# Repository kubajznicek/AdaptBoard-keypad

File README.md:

# AdaptBoard keypad

Custom macropad with swappable modules, based on Key Boar 2040.

## Features

- swappable modules
- 4x5 customizable grid
- serial communication

#### Different modules
- key switch module
- potentiometer module
- slide potentiometer module
- lcd module
- joystick module

## Parts list

#### Base of the keypad
- [Kee Boar 2040](https://www.adafruit.com/product/5302)
- [Analog multiplexer](https://www.laskakit.cz/analogovy-multiplexer-16-kanalu-cd74hc4067/)
- custom [PCB](./pcb/)
- 3D printed case
- [pin header](https://www.laskakit.cz/dupont-2x40pin-2-54-mm-pinovy-pas/)*
- [pin header](https://www.laskakit.cz/dupont-40pin-2-54-mm-pinovy-pas/)* for KB2040 and Analog multiplexer
- any USB-C cable

#### Modules
- keyboard switch (any standard keyboard switch should work)
- [potenciometr](https://www.laskakit.cz/psotenciometr-posuvny-10kohm--modul/)*
- [linear potenciometr](https://www.laskakit.cz/potenciometr-rk097n-3-10k-linearni-10k--/)*
- [analog multiplexer](https://www.laskakit.cz/analogovy-multiplexer-16-kanalu-cd74hc4067/)*
- [joystick](https://www.laskakit.cz/joystick-2d-modul/)*
- [OLED display](https://www.laskakit.cz/oled-displej-modry-128x32-0-91--i2c/?gad_source=1&gclid=Cj0KCQiA84CvBhCaARIsAMkAvkJ4arz2CuIuH9ewTWeozkwsCQH9d-Wme8BHi-cLq8MTYEL1yehATqgaArHrEALw_wcB)*
- [pin socket](https://www.laskakit.cz/dupont-2x20pin-2-54-mm-pinovy-pas--samice/)* 02x04
- 3D printed keycaps

<sub>*link to Czech e-shop. You may buy elsewhere, just make sure it is the same part model<sub>

## Build your own

for required parts see [Parts list](#parts-list)
Once you have all the parts, you can start building your own AdaptBoard keypad.

#### Soldering

1. Solder pin headers to the Kee Boar 2040 and to the Analog multiplexer
2. Solder first batch of headers to the custom PCB

3. Trim the headers on the Kee Boar 2040 and Analog multiplexer, so they are ~1mm above the PCB

Then solder the Kee Boar 2040 and Analog multiplexer to the back side of the PCB
4. Solder the remaining headers to the PCB

#### Assembling

@TODO

#### Programming
1. Install [CircuitPython](https://learn.adafruit.com/adafruit-kb2040/circuitpython) on your Kee Boar 2040 __Developed and tested on CircuitPython version 8.2.7__
2. Delete the `code.py` file from the CIRCUITPY drive
3. Upload our [firmware](./firmware/) to the CIRCUITPY drive
The final file structure should look like this:
```plaintext
CIRCUITPY
    analog_signal_processor.py
    boot_out.txt #circuitpy system file
    functions.py
    /lib
        /adafruit_display_text
        /adafruit_hid
        adafruit_pixelbuf.mpy
        neopixel.mpy
    main.py
    ssd1306_display.py
```
4. Go to [our App](https://adaptboard-c6996.web.app/) and create your own layout and configuration

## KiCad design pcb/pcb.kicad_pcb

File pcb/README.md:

# PCB

Here are all files related to the PCB design of the project.
The PCB is designed using KiCad.
The 1x1 modules are in the `1x1` folder with a panel of 25 modules for manufacturing.

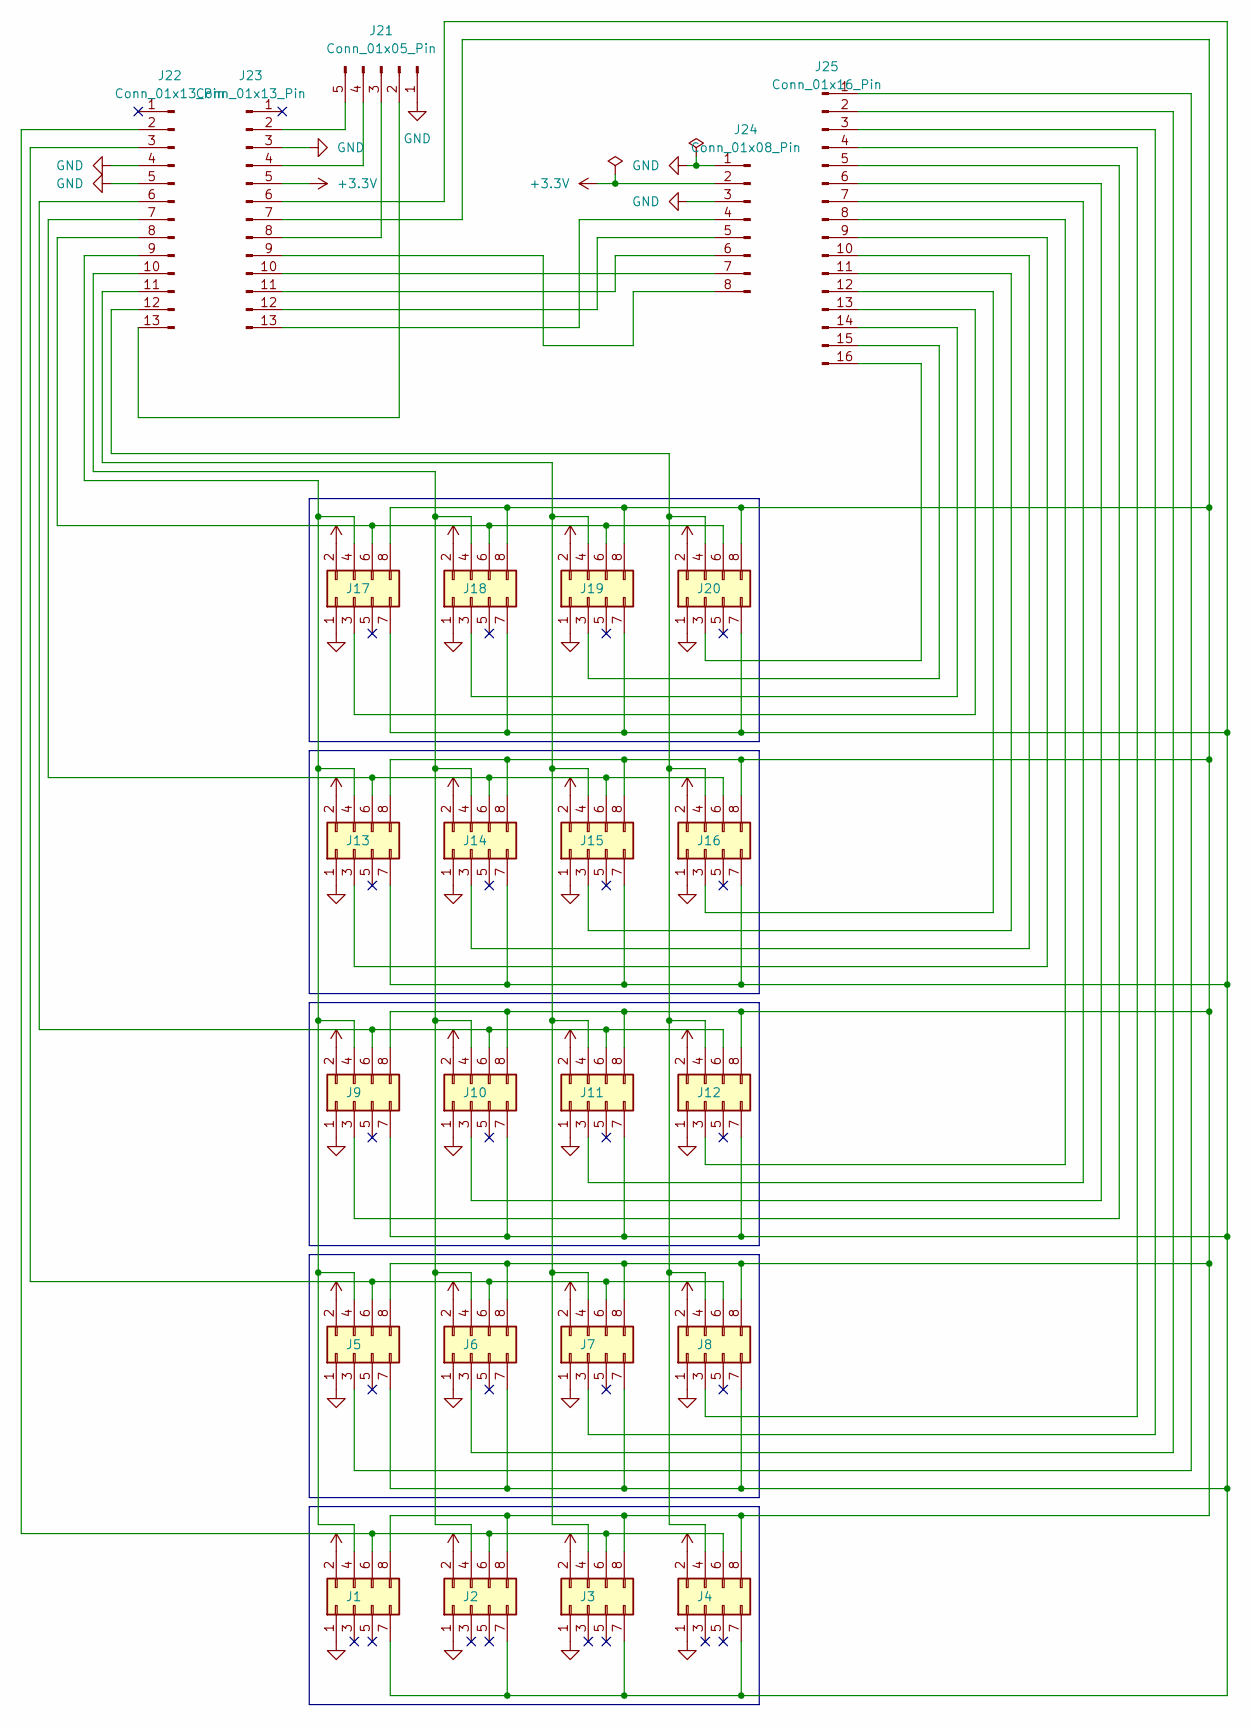
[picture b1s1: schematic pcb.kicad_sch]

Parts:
J1, J2, J3, J4, J5, J6, J7, J8, J9, J10, J11, J12, J13, J14, J15, J16, J17, J18, J19, J20: Conn_02x04_Odd_Even; PinHeader_2x04_P2.54mm_Vertical
J21: Conn_01x05_Pin; PinHeader_1x05_P2.54mm_Vertical
J22, J23: Conn_01x13_Pin; PinSocket_1x13_P2.54mm_Vertical
J24: Conn_01x08_Pin; PinSocket_1x08_P2.54mm_Vertical
J25: Conn_01x16_Pin; PinSocket_1x16_P2.54mm_Vertical

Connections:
+3.3V: J1.2, J2.2, J3.2, J4.2, J5.2, J6.2, J7.2, J8.2, J9.2, J10.2, J11.2, J12.2, J13.2, J14.2, J15.2, J16.2, J17.2, J18.2, J19.2, J20.2, J23.5, J24.2
GND: J1.1, J2.1, J3.1, J4.1, J5.1, J6.1, J7.1, J8.1, J9.1, J10.1, J11.1, J12.1, J13.1, J14.1, J15.1, J16.1, J17.1, J18.1, J19.1, J20.1, J21.1, J22.4, J22.5, J23.3, J24.1, J24.3
unnamed: J1.4, J5.4, J9.4, J13.4, J17.4, J22.9
unnamed: J1.6, J2.6, J3.6, J4.6, J22.2
unnamed: J1.7, J2.7, J3.7, J4.7, J5.7, J6.7, J7.7, J8.7, J9.7, J10.7, J11.7, J12.7, J13.7, J14.7, J15.7, J16.7, J17.7, J18.7, J19.7, J20.7, J23.6
unnamed: J1.8, J2.8, J3.8, J4.8, J5.8, J6.8, J7.8, J8.8, J9.8, J10.8, J11.8, J12.8, J13.8, J14.8, J15.8, J16.8, J17.8, J18.8, J19.8, J20.8, J23.7
unnamed: J10.3, J25.6
unnamed: J2.4, J6.4, J10.4, J14.4, J18.4, J22.10
unnamed: J9.6, J10.6, J11.6, J12.6, J22.6
unnamed: J11.3, J25.7
unnamed: J3.4, J7.4, J11.4, J15.4, J19.4, J22.11
unnamed: J12.3, J25.8
unnamed: J4.4, J8.4, J12.4, J16.4, J20.4, J22.12
unnamed: J13.3, J25.9
unnamed: J13.6, J14.6, J15.6, J16.6, J22.7
unnamed: J14.3, J25.10
unnamed: J15.3, J25.11
unnamed: J16.3, J25.12
unnamed: J17.3, J25.13
unnamed: J17.6, J18.6, J19.6, J20.6, J22.8
unnamed: J18.3, J25.14
unnamed: J19.3, J25.15
unnamed: J20.3, J25.16
unnamed: J21.2, J22.13
unnamed: J21.3, J23.8
unnamed: J21.4, J23.4
unnamed: J21.5, J23.2
unnamed: J5.6, J6.6, J7.6, J8.6, J22.3
unnamed: J23.9, J24.8
unnamed: J23.10, J24.7
unnamed: J23.11, J24.6
unnamed: J23.12, J24.5
unnamed: J23.13, J24.4
unnamed: J5.3, J25.1
unnamed: J6.3, J25.2
unnamed: J7.3, J25.3
unnamed: J8.3, J25.4
unnamed: J9.3, J25.5

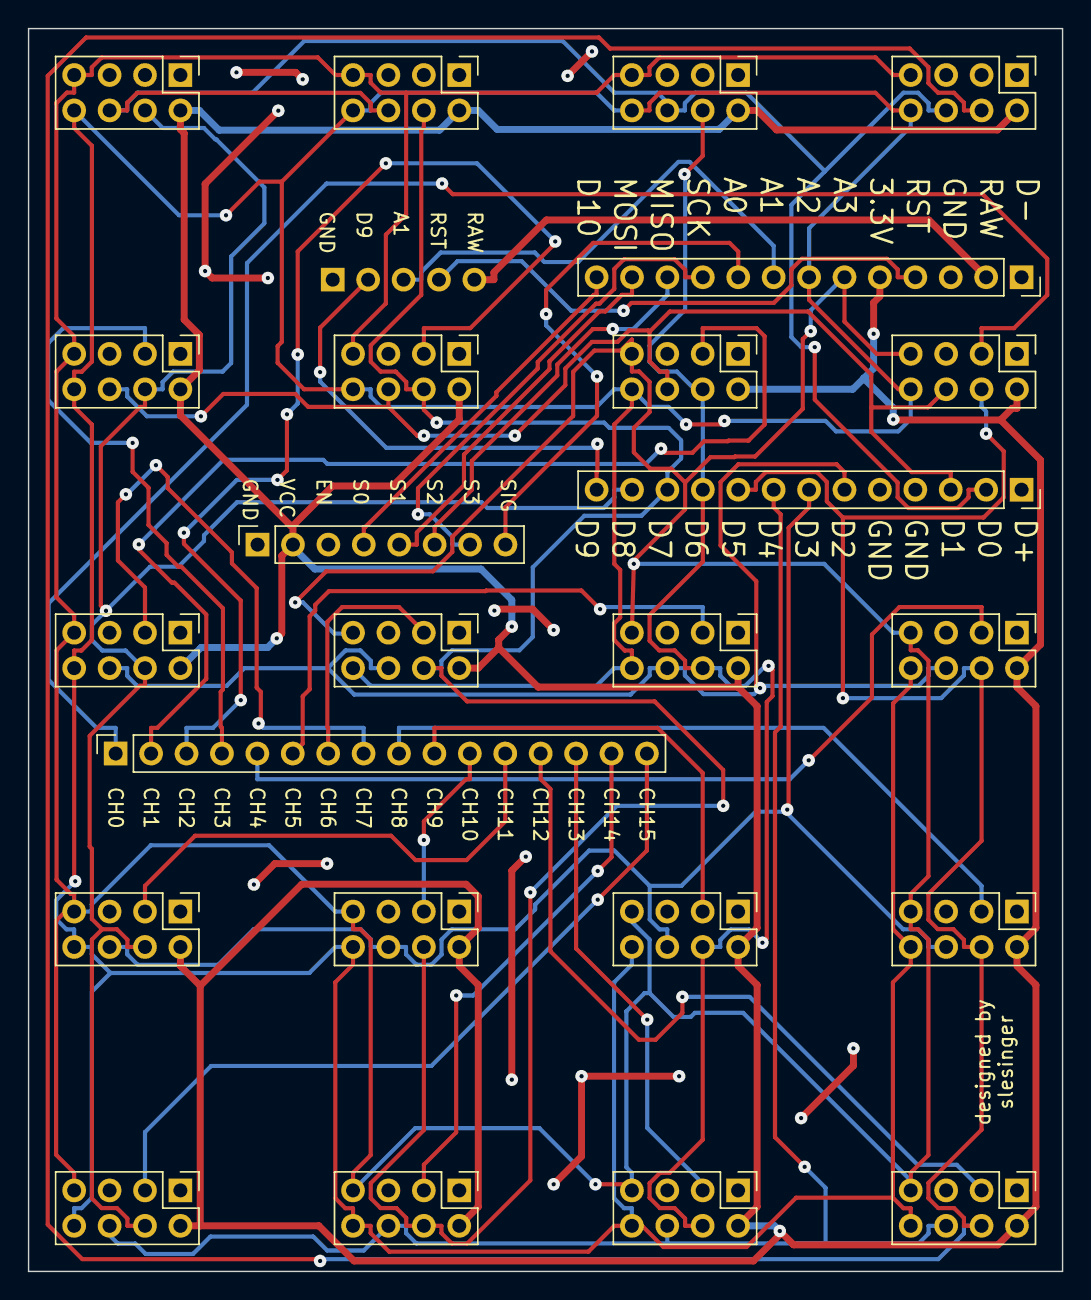
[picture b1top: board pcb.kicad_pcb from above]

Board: 2 copper layers, 74.2 x 89.1 mm, 25 parts (1 on the bottom side), 38 nets.

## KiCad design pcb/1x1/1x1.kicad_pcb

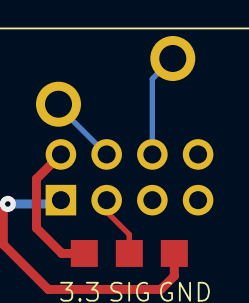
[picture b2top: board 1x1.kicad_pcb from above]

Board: 2 copper layers, 5 parts (1 on the bottom side), 5 nets.

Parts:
J1: Conn_02x04_Odd_Even; PinSocket_2x04_P2.54mm_Vertical
SW1: SW_Push; SW_Cherry_MX_Plate
TP1, TP2, TP3: TestPoint; TestPoint_Pad_1.5x1.5mm

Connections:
unnamed: J1.1, TP2.1
unnamed: J1.2, TP3.1
unnamed: J1.3, TP1.1
unnamed: J1.4, SW1.1
unnamed: J1.6, SW1.2

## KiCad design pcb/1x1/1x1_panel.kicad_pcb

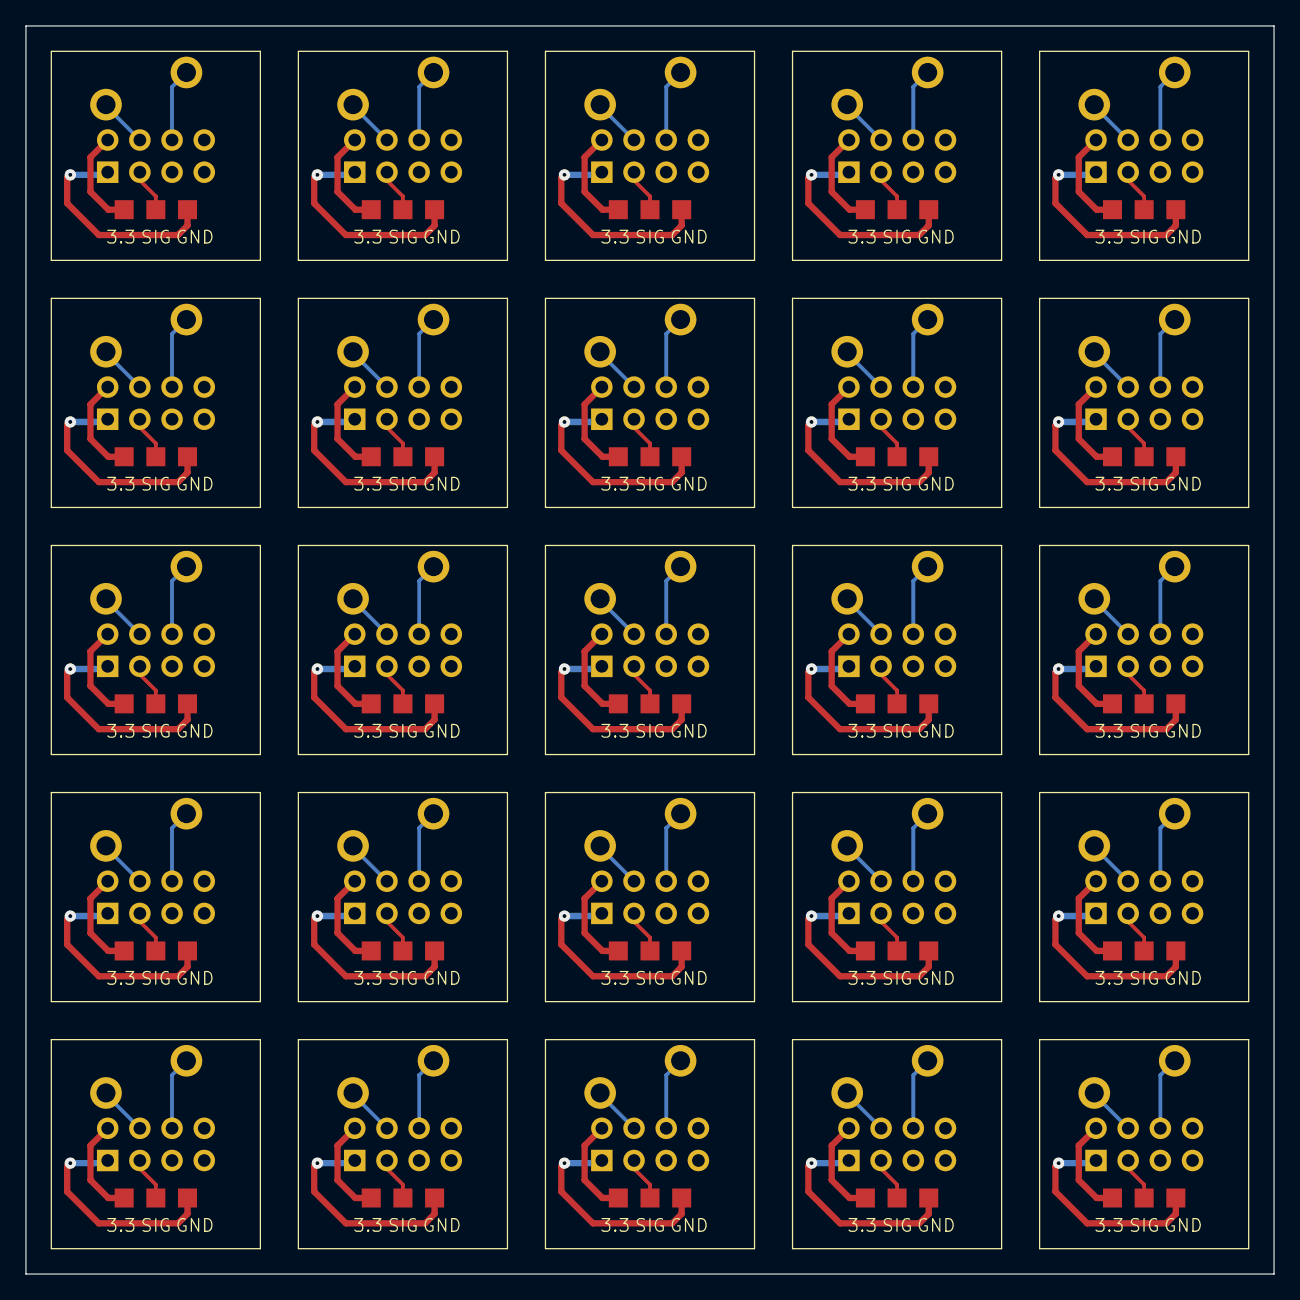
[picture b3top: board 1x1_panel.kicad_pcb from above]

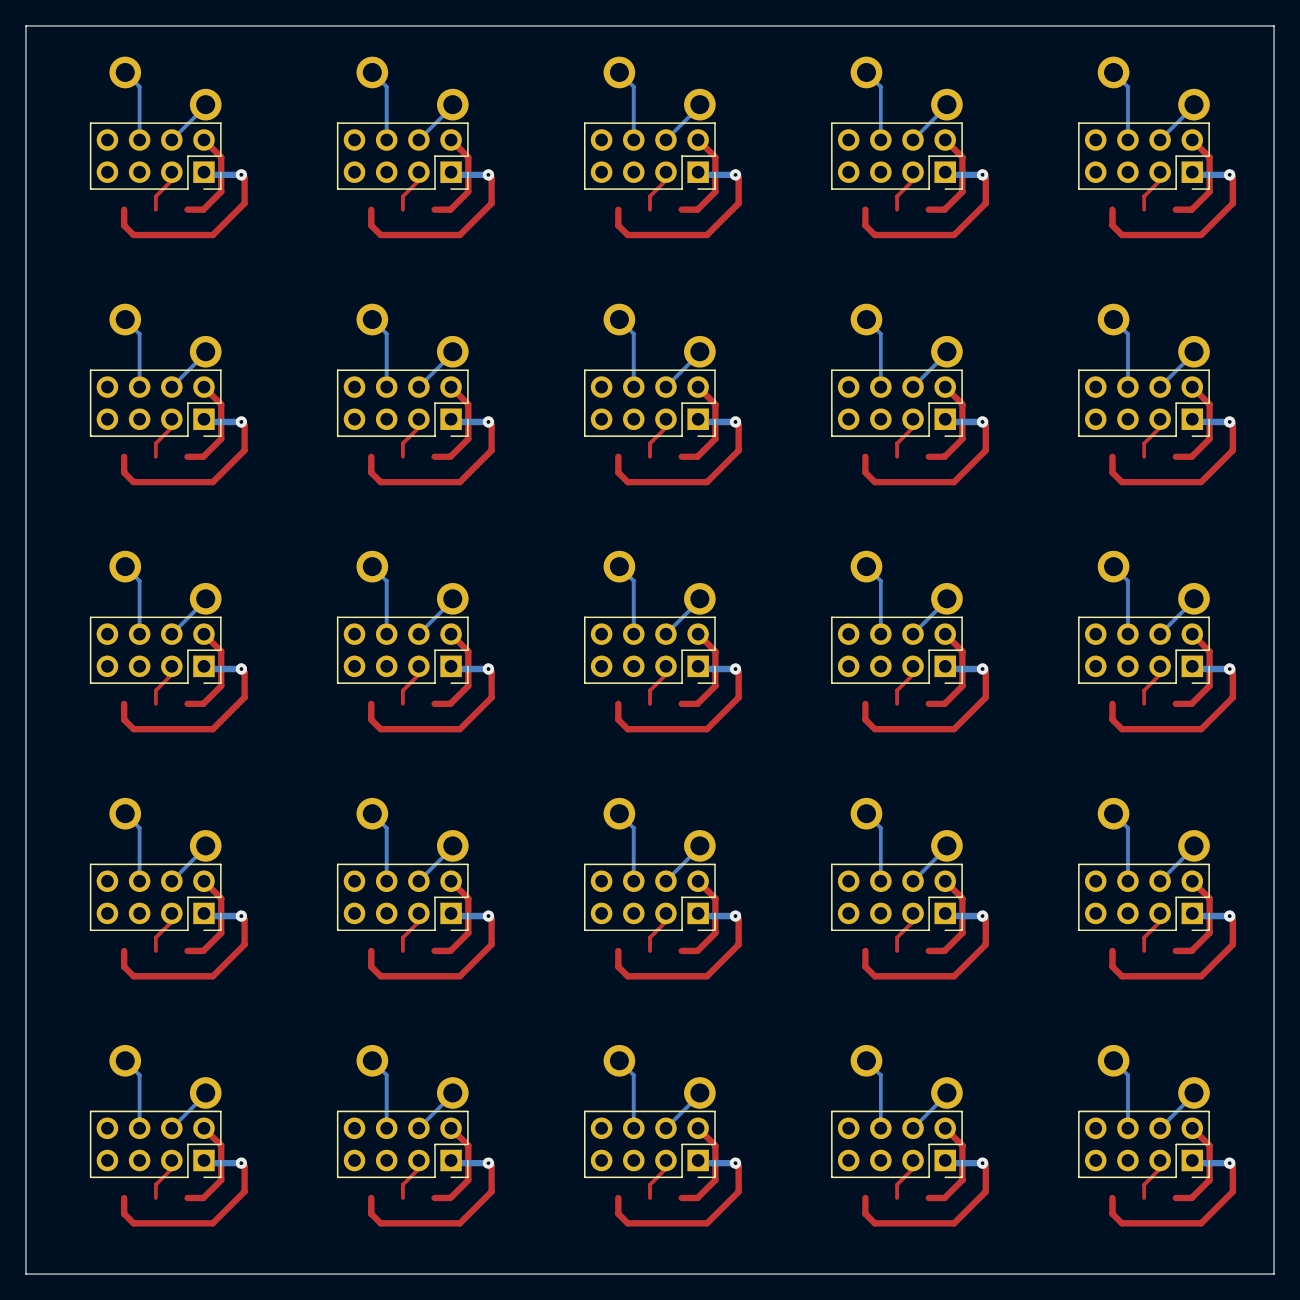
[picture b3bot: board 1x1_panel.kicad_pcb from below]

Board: 2 copper layers, 98.5 x 98.5 mm, 125 parts (25 on the bottom side), 5 nets.

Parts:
J1, J1#2, J2, J3, J4, J5, J6, J7, J8, J9, J10, J11, J12, J13, J14, J15, J16, J17, J18, J19, J20, J21, J22, J23, J24: Conn_02x04_Odd_Even; PinSocket_2x04_P2.54mm_Vertical
SW1, SW1#2, SW2, SW3, SW4, SW5, SW6, SW7, SW8, SW9, SW10, SW11, SW12, SW13, SW14, SW15, SW16, SW17, SW18, SW19, SW20, SW21, SW22, SW23, SW24: SW_Push; SW_Cherry_MX_Plate
TP1, TP1#2, TP2, TP2#2, TP3, TP3#2, TP4, TP5, TP6, TP7, TP8, TP9, TP10, TP11, TP12, TP13, TP14, TP15, TP16, TP17, TP18, TP19, TP20, TP21, TP22, TP23, TP24, TP25, TP26, TP27, TP28, TP29, TP30, TP31, TP32, TP33, TP34, TP35, TP36, TP37, TP38, TP39, TP40, TP41, TP42, TP43, TP44, TP45, TP46, TP47, TP48, TP49, TP50, TP51, TP52, TP53, TP54, TP55, TP56, TP57, TP58, TP59, TP60, TP61, TP62, TP63, TP64, TP65, TP66, TP67, TP68, TP69, TP70, TP71, TP72: TestPoint; TestPoint_Pad_1.5x1.5mm

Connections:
unnamed: J1.1, J1#2.1, J2.1, J3.1, J4.1, J5.1, J6.1, J7.1, J8.1, J9.1, J10.1, J11.1, J12.1, J13.1, J14.1, J15.1, J16.1, J17.1, J18.1, J19.1, J20.1, J21.1, J22.1, J23.1, J24.1, TP2.1, TP2#2.1, TP5.1, TP8.1, TP11.1, TP14.1, TP17.1, TP20.1, TP23.1, TP26.1, TP29.1, TP32.1, TP35.1, TP38.1, TP41.1, TP44.1, TP47.1, TP50.1, TP53.1, TP56.1, TP59.1, TP62.1, TP65.1, TP68.1, TP71.1
unnamed: J1.2, J1#2.2, J2.2, J3.2, J4.2, J5.2, J6.2, J7.2, J8.2, J9.2, J10.2, J11.2, J12.2, J13.2, J14.2, J15.2, J16.2, J17.2, J18.2, J19.2, J20.2, J21.2, J22.2, J23.2, J24.2, TP3.1, TP3#2.1, TP6.1, TP9.1, TP12.1, TP15.1, TP18.1, TP21.1, TP24.1, TP27.1, TP30.1, TP33.1, TP36.1, TP39.1, TP42.1, TP45.1, TP48.1, TP51.1, TP54.1, TP57.1, TP60.1, TP63.1, TP66.1, TP69.1, TP72.1
unnamed: J1.3, J1#2.3, J2.3, J3.3, J4.3, J5.3, J6.3, J7.3, J8.3, J9.3, J10.3, J11.3, J12.3, J13.3, J14.3, J15.3, J16.3, J17.3, J18.3, J19.3, J20.3, J21.3, J22.3, J23.3, J24.3, TP1.1, TP1#2.1, TP4.1, TP7.1, TP10.1, TP13.1, TP16.1, TP19.1, TP22.1, TP25.1, TP28.1, TP31.1, TP34.1, TP37.1, TP40.1, TP43.1, TP46.1, TP49.1, TP52.1, TP55.1, TP58.1, TP61.1, TP64.1, TP67.1, TP70.1
unnamed: J1.4, J1#2.4, J2.4, J3.4, J4.4, J5.4, J6.4, J7.4, J8.4, J9.4, J10.4, J11.4, J12.4, J13.4, J14.4, J15.4, J16.4, J17.4, J18.4, J19.4, J20.4, J21.4, J22.4, J23.4, J24.4, SW1.1, SW1#2.1, SW2.1, SW3.1, SW4.1, SW5.1, SW6.1, SW7.1, SW8.1, SW9.1, SW10.1, SW11.1, SW12.1, SW13.1, SW14.1, SW15.1, SW16.1, SW17.1, SW18.1, SW19.1, SW20.1, SW21.1, SW22.1, SW23.1, SW24.1
unnamed: J1.6, J1#2.6, J2.6, J3.6, J4.6, J5.6, J6.6, J7.6, J8.6, J9.6, J10.6, J11.6, J12.6, J13.6, J14.6, J15.6, J16.6, J17.6, J18.6, J19.6, J20.6, J21.6, J22.6, J23.6, J24.6, SW1.2, SW1#2.2, SW2.2, SW3.2, SW4.2, SW5.2, SW6.2, SW7.2, SW8.2, SW9.2, SW10.2, SW11.2, SW12.2, SW13.2, SW14.2, SW15.2, SW16.2, SW17.2, SW18.2, SW19.2, SW20.2, SW21.2, SW22.2, SW23.2, SW24.2

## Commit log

2023-10-19 readme
2023-10-22 added gitignore, blink neopixel examlpe
2023-10-30 added docs
2023-10-31 fix path in command
2023-11-09 kuba branch
2023-11-09 lukas branch
2023-11-09 filip branch
2023-11-10 Schafl, dve zkratky
2023-11-10 functions for reading chnnels from analog multiplexer
2023-11-12 fix SetChannel function, add LogChannel function, cc for testing
2023-11-13 fix SetChannel function
2023-11-13 add adafruit_hid lib
2023-11-13 pinout png, keypad matrix
2023-11-16 scaning multiplexer ports
2023-11-16 autohotkey trigger
2023-11-17 time.spleep decreased, add TODO
2023-11-18 naming conventions, AnalogSignalProcessor class
2023-11-18 benchmark
2023-11-20 experiment with triggered times in analog readings
2023-11-23 add custom pinout, tested spi pins for multiplexer control
2023-11-23 add kicad pcb folder
2023-11-24 add multiplexer symbol
2023-11-25 add matrix config file
2023-11-26 pcb schema
2023-11-28 Shcafl, dve zkratky
2023-11-28 renaming files, autokey testing
2023-11-30 scanning only defined analog channels
2023-12-01 add debug mode, move settings to config.py
2023-12-01 sync with remote
2023-12-01 Kuba CircuitPython code (#1)
    * kuba branch
    * ben
    * functions for reading chnnels from analog multiplexer
    * fix SetChannel function, add LogChannel function, cc for testing
    * fix SetChannel function
    * add adafruit_hid lib
2023-12-01 react app foundations
2023-12-01 fixed pin rotation on custom components
2023-12-02 add pcb footprints to pin headers
2023-12-07 react DnD
2023-12-09 light toggle automation
2023-12-09 current_value in analog read loop
2023-12-11 header in documentation fixed, pcb schematic done
2023-12-15 pcb edge cuts
2023-12-16 custom DnD
2023-12-16 add image to DnD
2023-12-21 Create a file that can be loaded into the Board, 1st version
2024-01-02 moved python files to firmware folder
2024-01-02 new way of generating app.py file; generation more automated with input array; generating matrix and analog actions
2024-01-04 autosave
2024-01-08 system status logging functions, ssd1306 display (libs + text render + bitmap render)
2024-01-15 pcb component placement
2024-01-16 first routing design
2024-01-24 pcb autosave, git ignore update
2024-01-31 fix multiplexer pin sockets placement
2024-02-01 skoro nic :)
2024-02-04 updated documentation
2024-02-04 display config, key not conigerd not longer crashes the main loop
2024-02-04 fixed
2024-02-07 updated pcb, 1x1 pcb
2024-02-13 moved 1x1 pcb folder
2024-02-13 colldonw for analog triggeres (experimental)
2024-02-14 moved analog channel settings, add analog channels state
2024-02-15 1x1 pcb updated
2024-02-15 pcb v2
2024-02-17 writie string functionality, backup before analog absolute maping
2024-02-17 removed app folder, new analog processing approach
2024-02-24 jostick mouse movement JUST FOR TESTING
2024-02-24 latest firmware version
2024-02-29 app folder
2024-02-29 clean uo
2024-02-29 clean up 2
2024-02-29 PCB v2, firmware - analog steps (#5)
    * kuba branch
    * lukas branch
    * ben
    * Schafl, dve zkratky
    * functions for reading chnnels from analog multiplexer
    * fix SetChannel function, add LogChannel function, cc for testing
2024-02-29 vue App
2024-02-29 Working shortcut, added pot and display options
    working transferring of shortcut from keyboard to AdBoard
    code design changes
    added potentiometer, display into dropdown
    dropdown generates everywhere (shuffle only top 2 lines)
    display content is not editable, only is there or not
2024-03-02 kicad version 8.0, 1x1 pcb
2024-03-11 corrected generation
2024-03-11 minor changes for proper functioning
2024-03-14 Whole Keyboard buttons available
2024-03-14 New Design progress - ADBoard element; Pinia
    ADBoard design and simple functionality
    Added by Pinia
2024-03-14 settings of AD-Board buttons - Potmetr
    working settings when selected Potmetr
    created files for other settings
2024-03-15 Mainly design for Display, Shuffle, Switch - text, Fn actions
    Display - functional = set display to true
    Shuffle - functional = set vars in ADKeys array
    Switch - functional - text and Fn functions - setting vars in Global variables
2024-03-15 Not staged files for previous update
2024-03-20 Config file, SCBoard
    Creating config file
    Created SCBoard for adding shortcut
    changes in styling and its dependences
2024-03-21 Functionality improvements
    Fn functions, write text, right pin for analog
2024-03-21 updated docs
2024-03-21 BugFix, design, Save as
    Not supported Czech chars in switch text
    Save as button for config file
2024-03-23 pcb 1x1 sync
2024-03-24 pcb restored, documentation photos
2024-04-01 rotated pcb, pcb documentation
2024-04-02 Cleaning of files and code
    Deleted not used files
    No analog on bottom line - can't have pot or shuffle
    Slight changes in code
2024-04-09 1x1 pcb update
2024-04-09 1x1 pcb update, pcb docs
2024-04-10 add boot.py, safe mode docs
2024-04-11 new version of app
    Compatible with last version of firmware
2024-04-15 type checking, usb_storage
2024-04-18 link to firebase app
2024-04-18 Final Push Firebase hosting proceeded
2024-04-18 3D models first commit
2024-04-18 3D models only
2024-04-20 removed old pcb files, examples in config.py
2024-06-28 gtid numbers
2024-09-28 Bump rollup from 4.12.0 to 4.22.5 in /app
    Bumps [rollup](https://github.com/rollup/rollup) from 4.12.0 to 4.22.5.
    - [Release notes](https://github.com/rollup/rollup/releases)
    - [Changelog](https://github.com/rollup/rollup/blob/master/CHANGELOG.md)
    - [Commits](https://github.com/rollup/rollup/compare/v4.12.0...v4.22.5)
    ---
    updated-dependencies:
2024-09-28 Bump rollup from 4.12.0 to 4.22.5 in /app (#10)
    Bumps [rollup](https://github.com/rollup/rollup) from 4.12.0 to 4.22.5.
    - [Release notes](https://github.com/rollup/rollup/releases)
    - [Changelog](https://github.com/rollup/rollup/blob/master/CHANGELOG.md)
    - [Commits](https://github.com/rollup/rollup/compare/v4.12.0...v4.22.5)
    ---
    updated-dependencies:
2024-11-14 Bump braces from 3.0.2 to 3.0.3 in /app
    Bumps [braces](https://github.com/micromatch/braces) from 3.0.2 to 3.0.3.
    - [Changelog](https://github.com/micromatch/braces/blob/master/CHANGELOG.md)
    - [Commits](https://github.com/micromatch/braces/compare/3.0.2...3.0.3)
    ---
    updated-dependencies:
    - dependency-name: braces
2024-11-14 Bump braces from 3.0.2 to 3.0.3 in /app (#11)
    Bumps [braces](https://github.com/micromatch/braces) from 3.0.2 to 3.0.3.
    - [Changelog](https://github.com/micromatch/braces/blob/master/CHANGELOG.md)
    - [Commits](https://github.com/micromatch/braces/compare/3.0.2...3.0.3)
    ---
    updated-dependencies:
    - dependency-name: braces
2025-02-07 Rename IMG20250207164130.jpg to kuba_keycaps.jpg
2025-04-19 Create LICENSE
2026-02-07 add pcb backups folders to itignore
2026-02-07 removed pcb backups
2026-02-10 configuration backup
2026-02-10 sending anlalog values over serial
2026-02-10 serial listener config
2026-02-10 serial listener
2026-03-02 big clean up
2026-03-02 updated gitignore
2026-03-02 updated dependencies and firebase config
2026-03-02 renamed 3d models, cleaned up 3d models, add keycaps models
2026-04-08 updated dependencies
